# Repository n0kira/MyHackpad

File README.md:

# Nokira's Hackpad!
Simple macropad with 6 keys, 1 rotary encoder and an OLED Display.

This is an open-case hackpad. You could say it was because I don't know how to build a case... maybe. But I like how  everything turned out.

#### Here is a [showcase](https://youtu.be/H9pZjf9lS04) of the finished hackpad (will change once I build it IRL) 

###### Built for Stardance!! [Project page here](https://stardance.hackclub.com/projects/50923)

---

# PCB

Made in KiCad!

# Schematic

Made in KiCad!

# Case

Made in Fusion!

# Firmware

QMK was used for everything.
The features of this hackpad are:
- Rotary encoder to change volume
- OLED disaply to show last action
- 6 Keys for macros

### The macros are:

```
┌──────┬──────┬──────┐
│ PREV │ PLAY │ NEXT │
├──────┼──────┼──────┤
│  F13 │  F14 │ LOCK │
└──────┴──────┴──────┘
```

- PREV > Previous Media
- PLAY > Play or Stop current Media
- NEXT > Next Media
- F13 > Free Macro Mey
- F14 > Free Macro Key
- LOCK > Lock Screen

# Bill Of Materials

| Component | Quantity |
| :--- | :---: |
| 1N4148 Diodes | 6 |
| MX-Style switches | 6 |
| SK6812 MINI-E LEDs | 6 |
| EC11 Rotary encoder | 1 |
| 0.91 inch OLED display | 1 |
| Seeed XIAO RP2040 | 1 |

# Extra notes:

Please keep in mind this is my first project of this kind. I never touched KiCad nor Fusion before.
This was made as a learning project to get started into this world. In the future I will continue learning and hopfully deliver more polished projects :)

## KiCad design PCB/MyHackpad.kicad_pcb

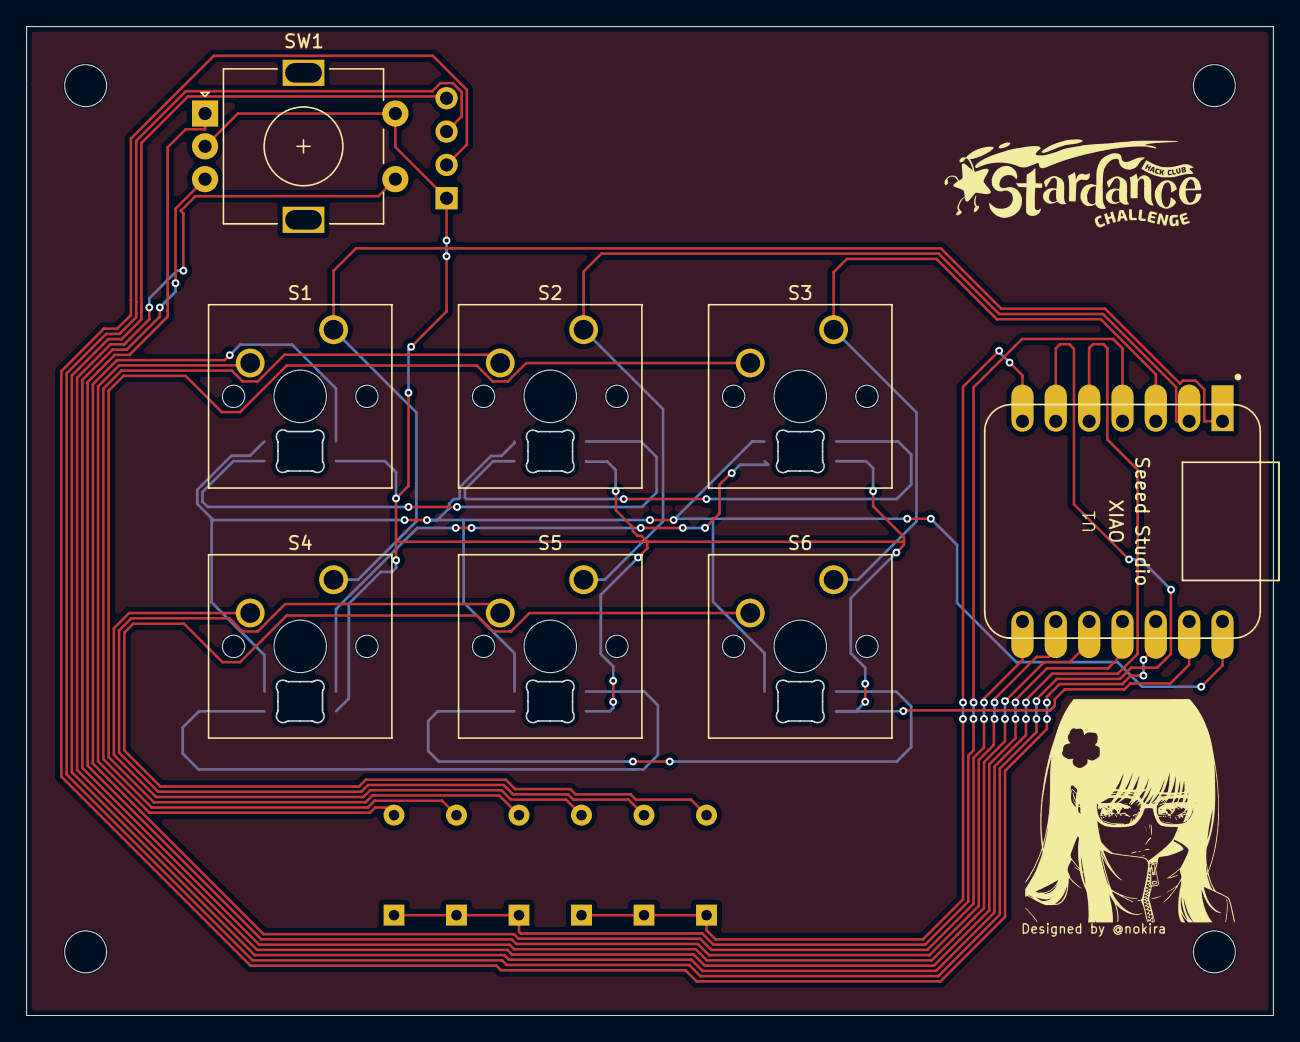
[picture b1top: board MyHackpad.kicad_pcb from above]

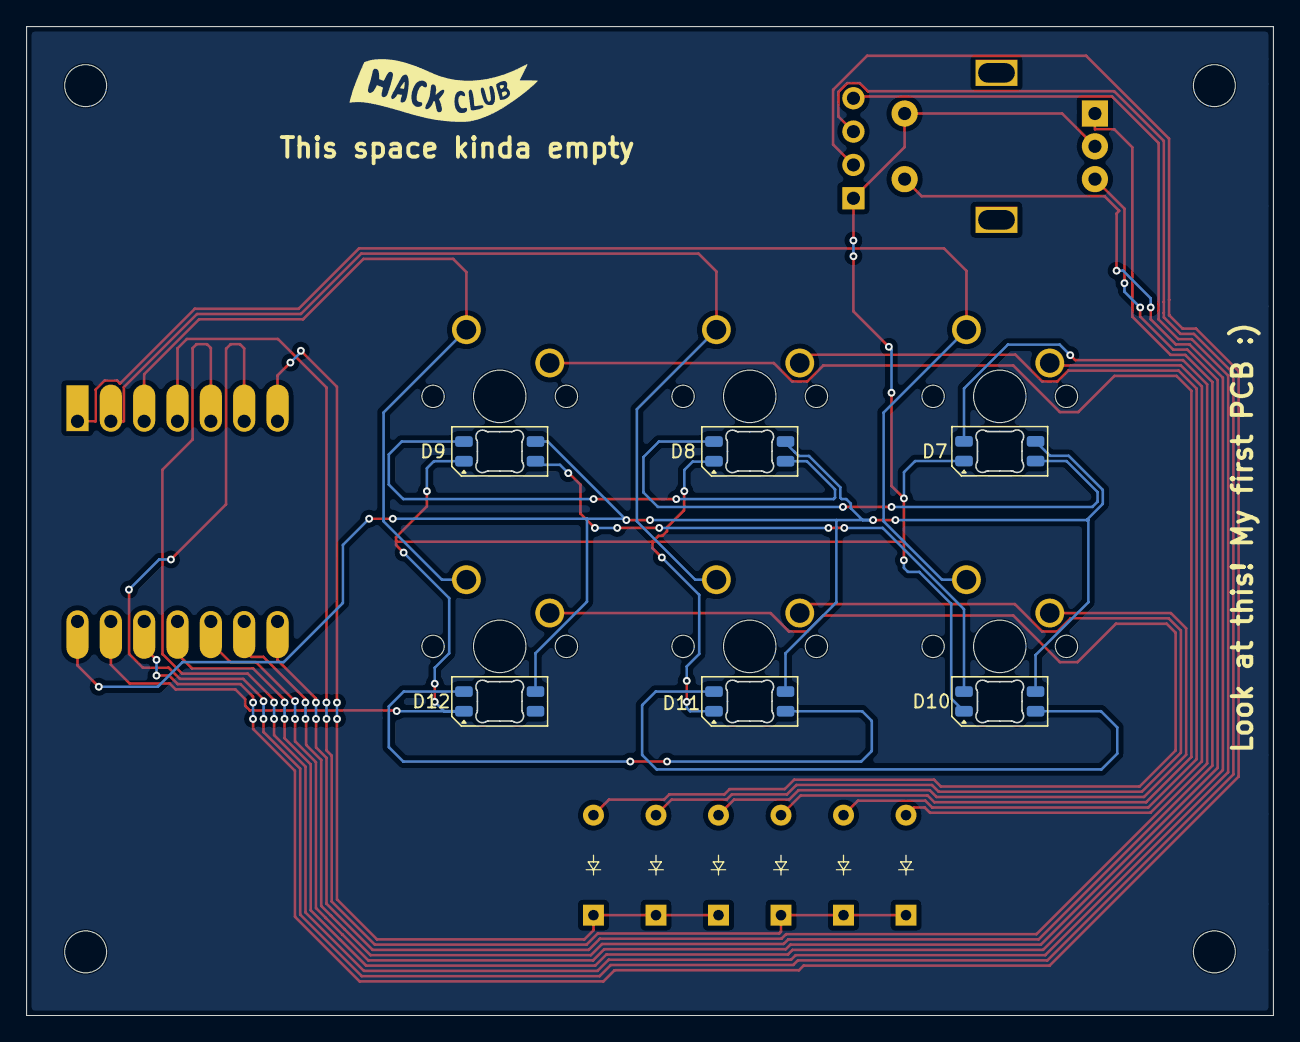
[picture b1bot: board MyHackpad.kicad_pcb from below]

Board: 2 copper layers, 95.0 x 75.3 mm, 21 parts (12 on the bottom side), 25 nets.

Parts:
D1, D2, D3, D4, D5, D6: Diode_DO-35
D7, D8, D9, D10, D11, D12: SK6812MINI-E; LED_SK6812MINI-E_3.2x2.8mm_P1.5mm_ReverseMount
J1: OLED_128x32
S1, S2, S3, S4, S5, S6: SW_Cherry_MX_1.00u_PCB
SW1: RotaryEncoder_Switch; RotaryEncoder_Alps_EC11E-Switch_Vertical_H20mm
U1: MOUDLE-SEEEDUINO-XIAO; XIAO-Generic-Hybrid-14P-2.54-21X17.8MM

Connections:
COLUMN_0: S1.1, S4.1, U1.1 (PA02_A0_D0)
COLUMN_1: S2.1, S5.1, U1.2 (PA4_A1_D1)
COLUMN_2: S3.1, S6.1, U1.3 (PA10_A2_D2)
ENCODER_A: SW1.A, U1.9 (PA7_A8_D8_SCK)
ENCODER_B: SW1.B, U1.10 (PA5_A9_D9_MISO)
ENCODER_S1: SW1.S1, U1.11 (PA6_A10_D10_MOSI)
GND: D7.1 (VSS), D8.1 (VSS), D9.1 (VSS), D10.1 (VSS), D11.1 (VSS), D12.1 (VSS), J1.1 (GND), SW1.C, SW1.S2, U1.13 (GND)
LEDs_DIN: D7.2 (DIN), U1.8 (PB09_A7_D7_RX)
LEDs_VDD: D7.3 (VDD), D8.3 (VDD), D9.3 (VDD), D10.3 (VDD), D11.3 (VDD), D12.3 (VDD), U1.14 (5V)
unnamed: D1.2 (A), S1.2
unnamed: D2.2 (A), S2.2
unnamed: D3.2 (A), S3.2
unnamed: D4.2 (A), S4.2
unnamed: D5.2 (A), S5.2
unnamed: D6.2 (A), S6.2
unnamed: D7.4 (DOUT), D8.2 (DIN)
unnamed: D8.4 (DOUT), D9.2 (DIN)
unnamed: D9.4 (DOUT), D10.2 (DIN)
unnamed: D10.4 (DOUT), D11.2 (DIN)
unnamed: D11.4 (DOUT), D12.2 (DIN)
OLED_SCL: J1.3 (SCL), U1.6 (PA9_A5_D5_SCL)
OLED_SDA: J1.4 (SDA), U1.5 (PA8_A4_D4_SDA)
OLED_VCC: J1.2 (VCC), U1.12 (3V3)
ROW_0: D1.1 (K), D2.1 (K), D3.1 (K), U1.4 (PA11_A3_D3)
ROW_1: D4.1 (K), D5.1 (K), D6.1 (K), U1.7 (PB08_A6_D6_TX)

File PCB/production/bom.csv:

Designator,Footprint,Quantity,Value,LCSC Part #
"D1, D2, D3, D4, D5, D6",Diode_DO-35,6,~,
"D10, D11, D12, D7, D8, D9",LED_SK6812MINI-E_3.2x2.8mm_P1.5mm_ReverseMount,6,SK6812MINI-E,
J1,OLED_128x32,1,OLED_128x32,
"S1, S2, S3, S4, S5, S6",SW_Cherry_MX_1.00u_PCB,6,~,
SW1,RotaryEncoder_Alps_EC11E-Switch_Vertical_H20mm,1,RotaryEncoder_Switch,
U1,XIAO-Generic-Hybrid-14P-2.54-21X17.8MM,1,MOUDLE-SEEEDUINO-XIAO,
